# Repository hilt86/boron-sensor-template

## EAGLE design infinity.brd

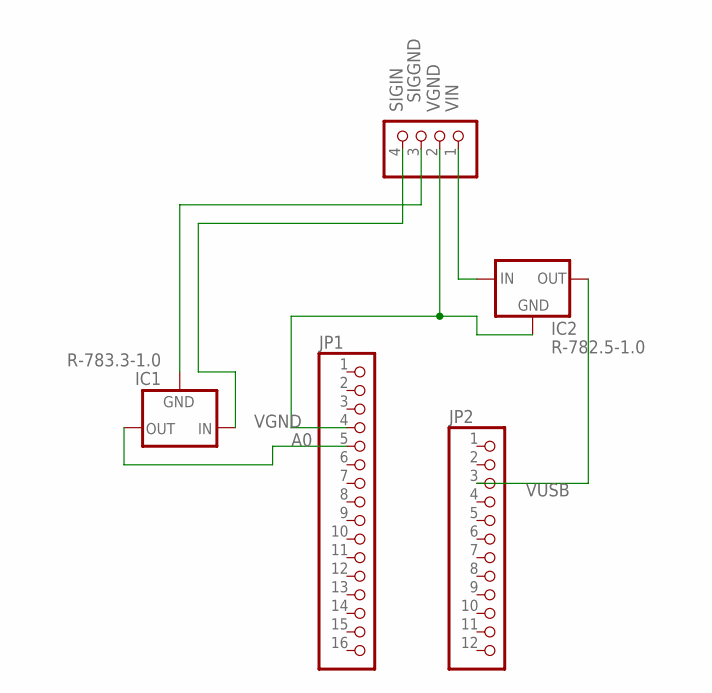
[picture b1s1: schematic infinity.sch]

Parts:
IC1: R-783.3-1.0; SIP3
IC2: R-782.5-1.0; SIP3
JP1: PINHD-1X16; 1X16
JP2: PINHD-1X12; 1X12
SIGGND: PINHD-1X4; 1X04

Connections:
A0: IC1.3 (OUT), JP1.5
unnamed: IC1.2 (GND), SIGGND.3
SIGIN: IC1.1 (IN), SIGGND.4
VGND: IC2.2 (GND), JP1.4, SIGGND.2
VIN: IC2.1 (IN), SIGGND.1
VUSB: IC2.3 (OUT), JP2.3

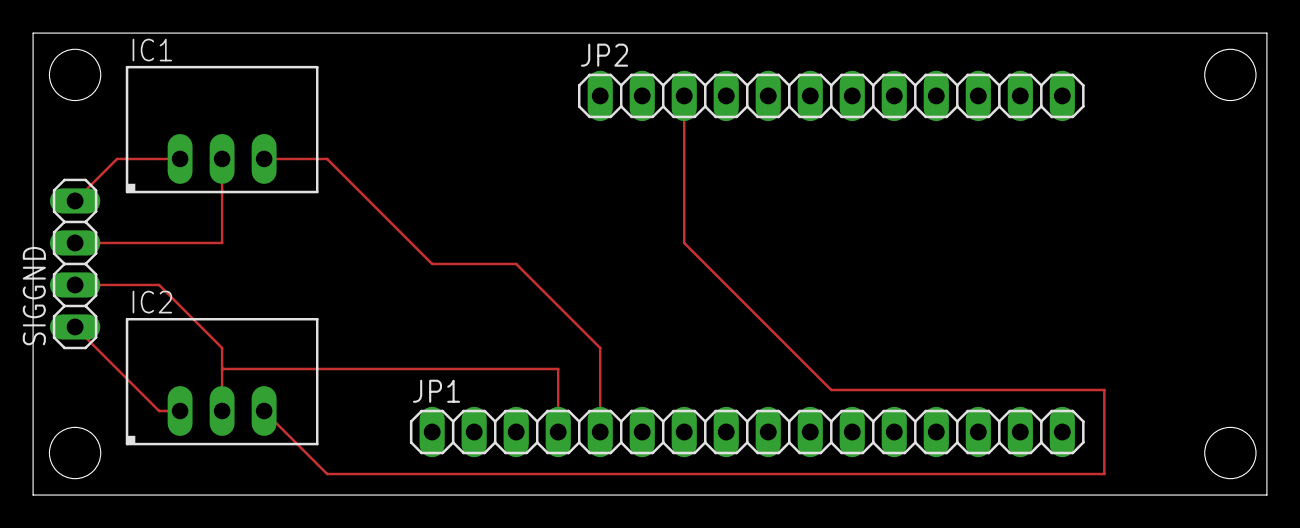
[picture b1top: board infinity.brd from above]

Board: 2 copper layers, 74.6 x 27.9 mm, 5 parts (0 on the bottom side), 6 nets.

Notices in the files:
parts and their libraries:
r-78xx_10: (c) 2015 Samuel Lourenço
